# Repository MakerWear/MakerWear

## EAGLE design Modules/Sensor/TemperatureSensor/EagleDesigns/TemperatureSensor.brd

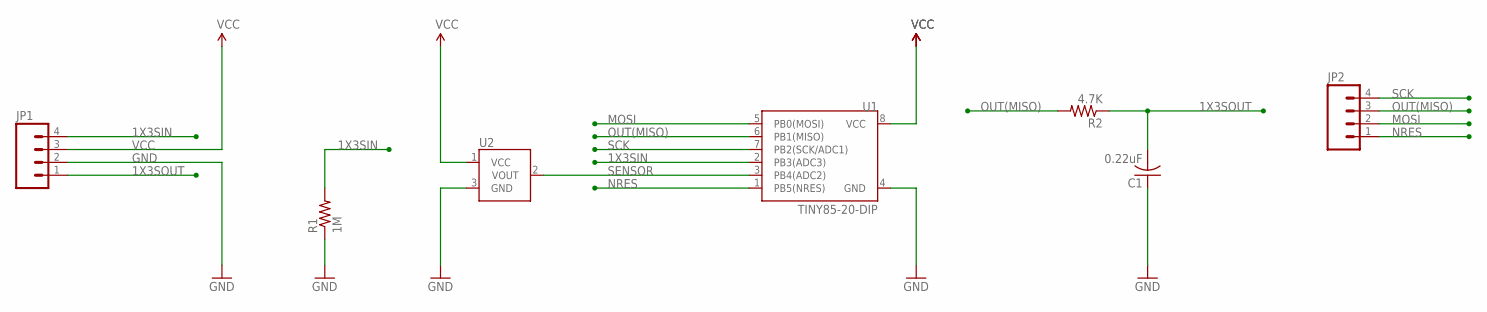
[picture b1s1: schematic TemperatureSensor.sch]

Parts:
C1: 0.22uF; C0402
JP1, JP2: M04PTH; 1X04
R1: 1M; R0603
R2: 4.7K; R0603
U1: TINY85-20-DIP; DIP08
U2: TMP36GT9; TO-92

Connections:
1X3SIN: JP1.4, R1.2, U1.2 (PB3(ADC3))
1X3SOUT: C1.2, JP1.1, R2.1
GND: C1.1, JP1.2, R1.1, U1.4 (GND), U2.3 (GND)
MOSI: JP2.2, U1.5 (PB0(MOSI))
NRES: JP2.1, U1.1 (PB5(NRES))
OUT(MISO): JP2.3, R2.2, U1.6 (PB1(MISO))
SCK: JP2.4, U1.7 (PB2(SCK/ADC1))
SENSOR: U1.3 (PB4(ADC2)), U2.2 (VOUT)
VCC: JP1.3, U1.8 (VCC), U2.1 (VCC)

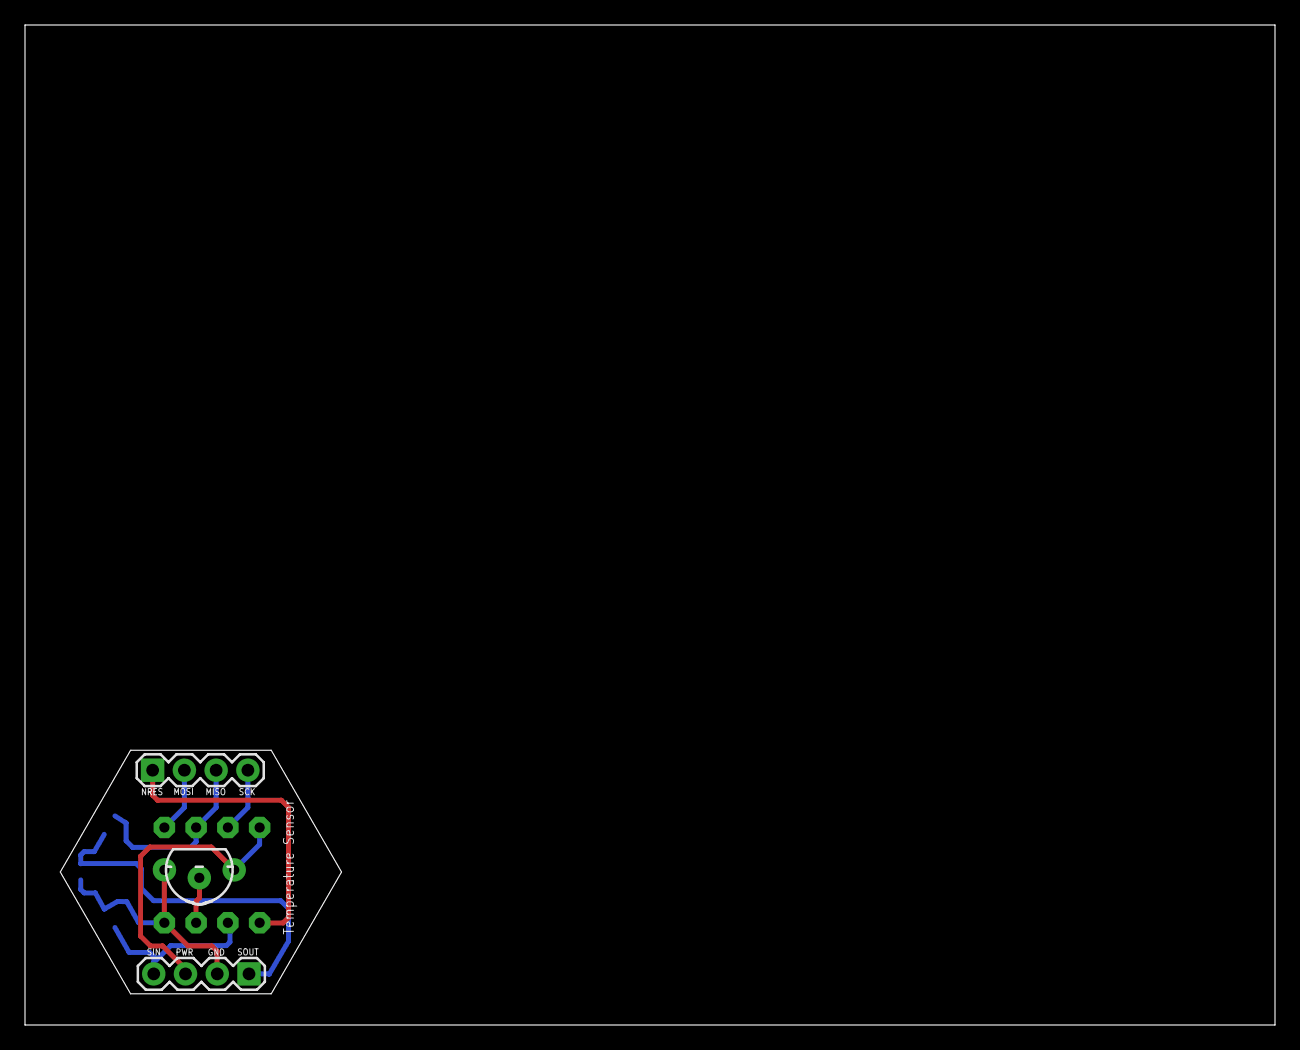
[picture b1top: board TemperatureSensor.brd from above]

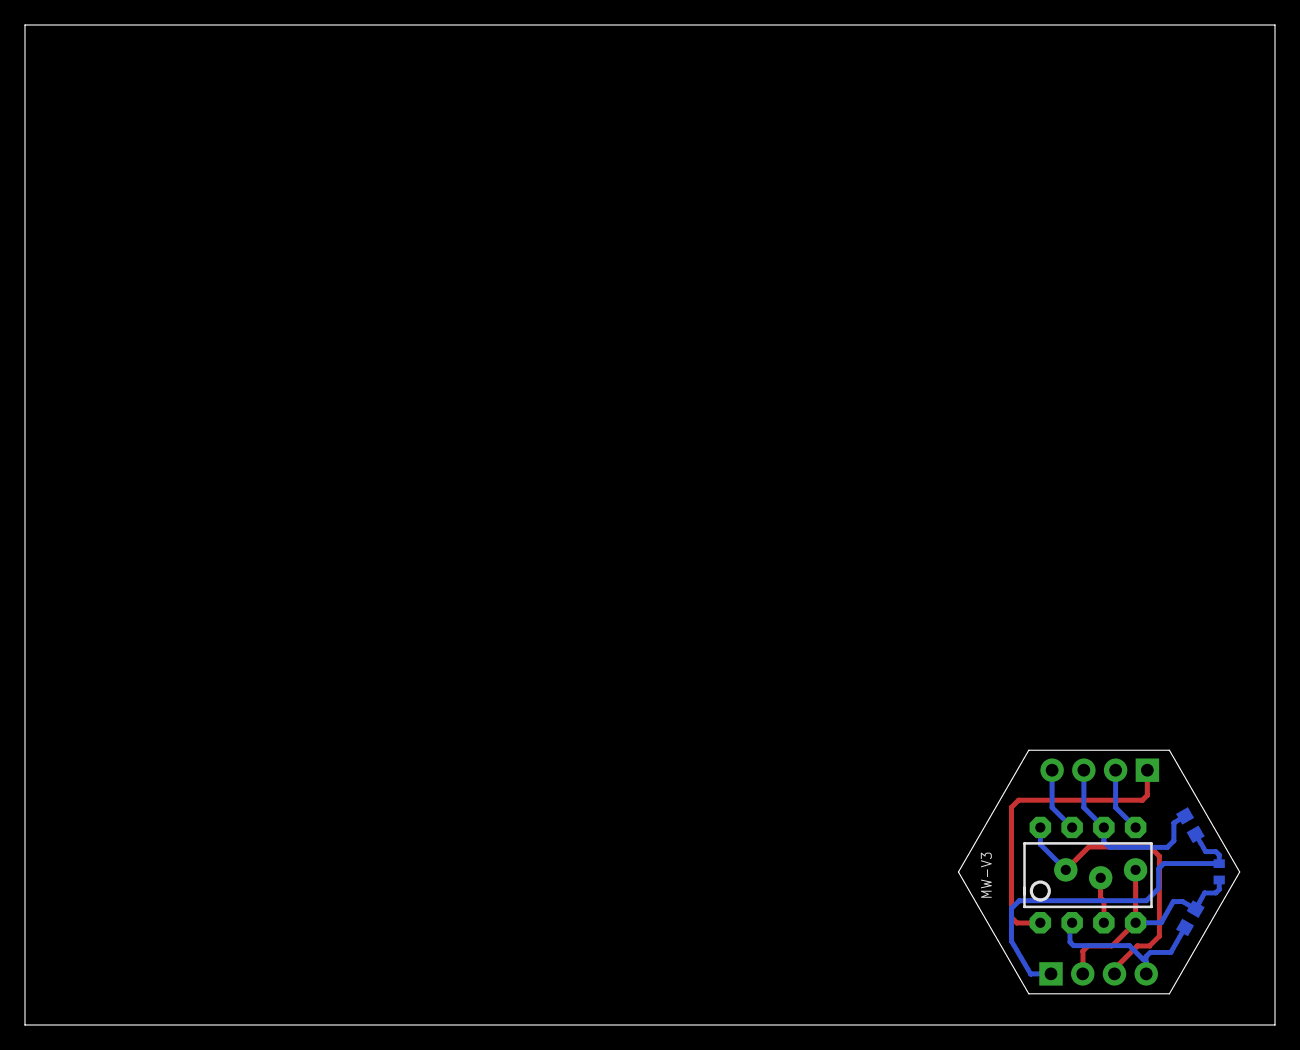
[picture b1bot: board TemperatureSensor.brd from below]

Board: 2 copper layers, 100.0 x 80.0 mm, 7 parts (4 on the bottom side), 9 nets.

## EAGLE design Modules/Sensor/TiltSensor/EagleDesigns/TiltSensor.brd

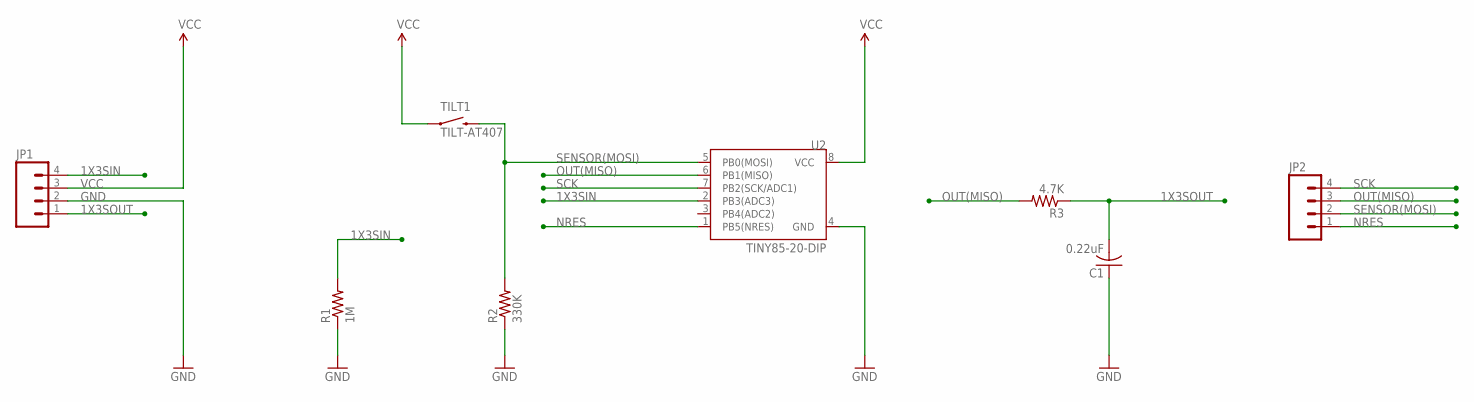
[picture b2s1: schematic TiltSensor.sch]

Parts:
C1: 0.22uF; C0402
JP1, JP2: M04PTH; 1X04
R1: 1M; R0603
R2: 330K; R0603
R3: 4.7K; R0603
TILT1: TILT-AT407
U2: TINY85-20-DIP; DIP08

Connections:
1X3SIN: JP1.4, R1.2, U2.2 (PB3(ADC3))
1X3SOUT: C1.2, JP1.1, R3.1
GND: C1.1, JP1.2, R1.1, R2.1, U2.4 (GND)
NRES: JP2.1, U2.1 (PB5(NRES))
OUT(MISO): JP2.3, R3.2, U2.6 (PB1(MISO))
SCK: JP2.4, U2.7 (PB2(SCK/ADC1))
SENSOR(MOSI): JP2.2, R2.2, TILT1.P$2 (2), U2.5 (PB0(MOSI))
VCC: JP1.3, TILT1.P$1 (1), U2.8 (VCC)

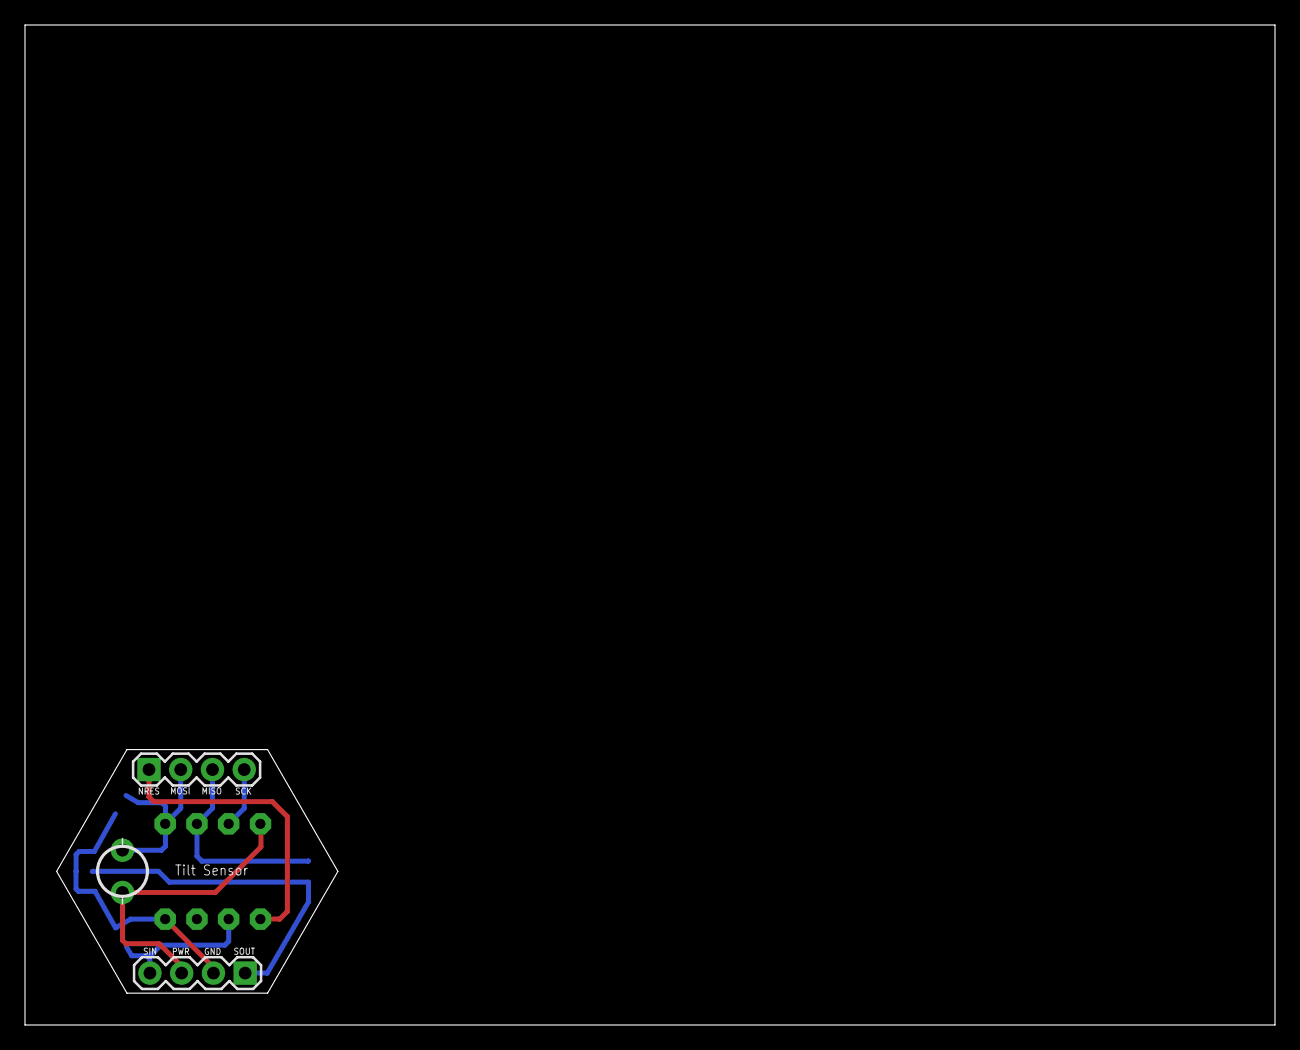
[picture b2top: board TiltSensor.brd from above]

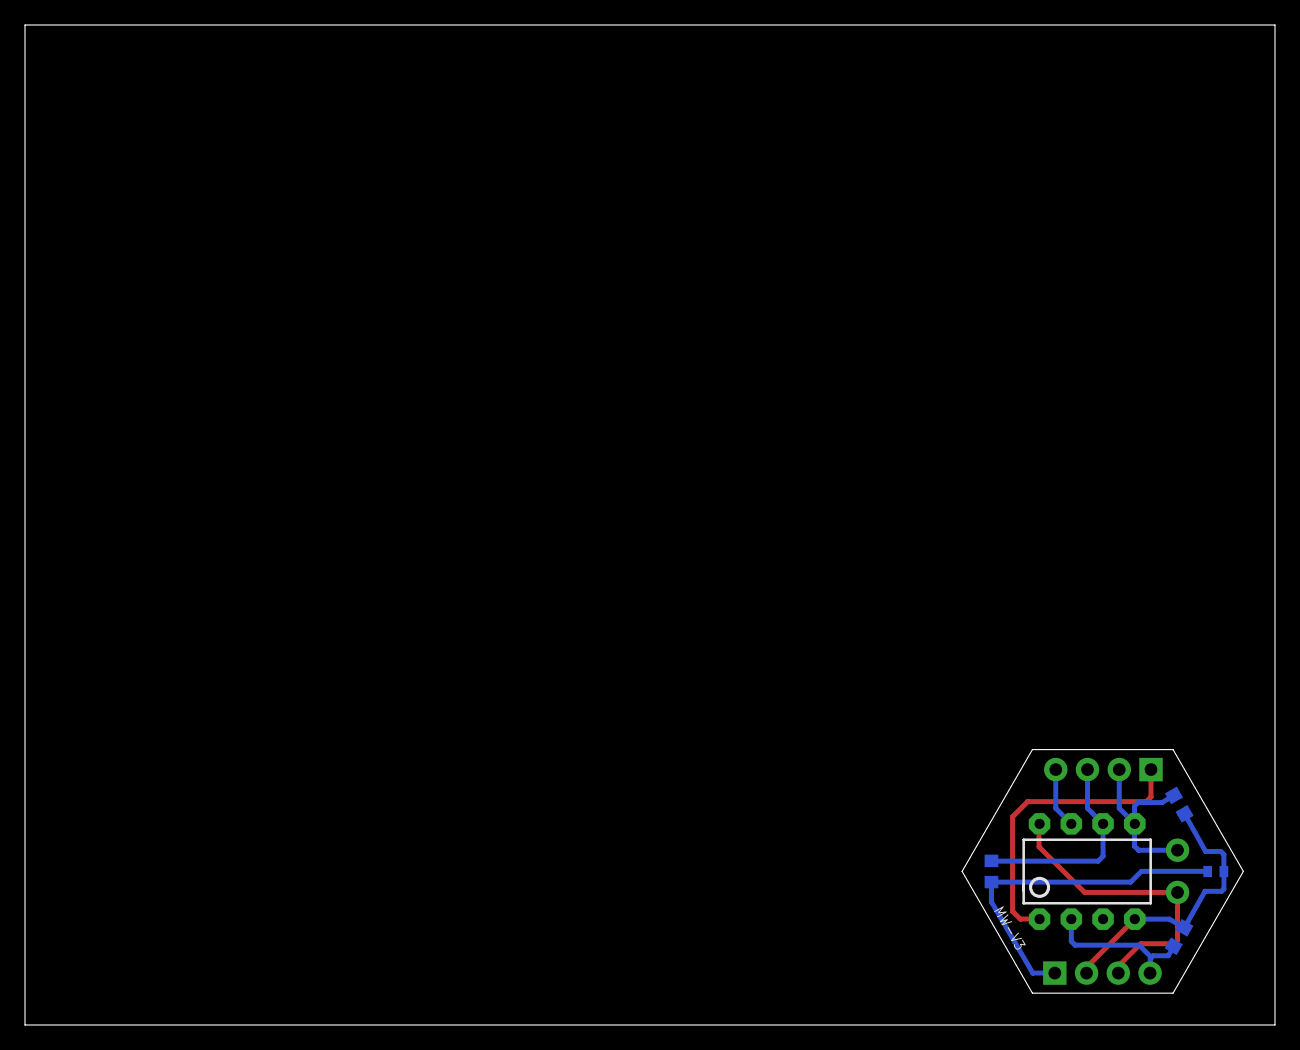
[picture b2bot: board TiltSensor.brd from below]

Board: 2 copper layers, 100.0 x 80.0 mm, 8 parts (5 on the bottom side), 8 nets.

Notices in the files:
parts and their libraries:
SparkFun-Connectors: Licensing: Creative Commons ShareAlike 4.0 International - https://creativecommons.org/licenses/by-sa/4.0
